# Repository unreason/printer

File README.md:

Printer
=======

Parts and components for a 3D printer

/fsr_endstop - an MSP430-based FSR endstop controller board. More documentation at http://www.unreasonmachines.com/msp430-fsr-endstop-controller-for-3d-printers/

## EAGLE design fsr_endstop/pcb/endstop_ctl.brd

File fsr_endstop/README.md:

FSR_endstop
=======

This is a small controller board for FSR bed leveling sensors for delta 3D printers such as Kossel. More detailed documentation at http://www.unreasonmachines.com/msp430-fsr-endstop-controller-for-3d-printers/.

This specific revision of the PCB hasn't been tested yet (PCBs have been ordered already) - but an earlier version with identical schematics but different layout is running just fine in my Kossel right now. Still, use at your own risk.

## Bill of materials

Name     | Part #                                | Qty |
---------|---------------------------------------|-----|
C1       | 100n 0603 capacitor                   | 1   | 
J1       | 3-pin JST PH right angle connector    | 1   | 
J2,J3,J4 | 2-pin JST PH right angle connector    | 3   |
J5       | 6-pin 1.27mm right angle connector    | 1   |
R1,R2,R3 | 10K 0603 resistor                     | 3   |
R4       | 1.5K 0603 resistor                    | 1   |
R5       | 47K 0603 resistor                     | 1   |
TOUCH    | 0603 2mA LED                          | 1   |
U1       | MSP430G2553 MCU, 20-pin SSOP          | 1   |

Tested with Interlink 30-81794 FSRs, but any similar sized FSR should work, possibly with minor changes to the filter coefficients in code.

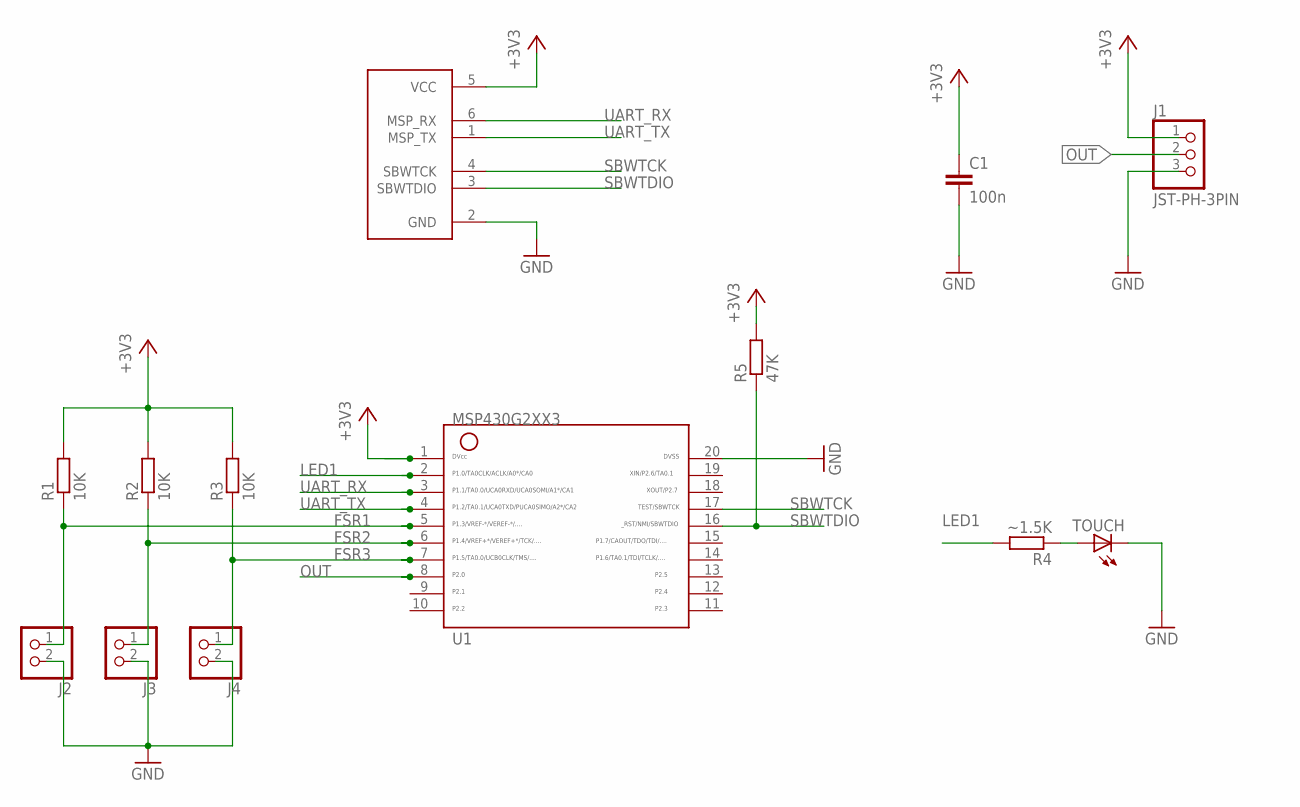
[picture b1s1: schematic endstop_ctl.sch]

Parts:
C1: 100n; C0603
J1: JST-PH-3PIN; JST-PH-3PIN-PTH-RA
J2, J3, J4: JST_2PIN-THM-RA; JST-PH-2-THM-RA
J5: MSP-SBWPTH; MSP-SBW-0.05-PTH-90DEG
R1, R2, R3: 10K; R0603
R4: ~1.5K; R0603
R5: 47K; R0603
TOUCH: LED0603; LED-0603
U1: G2XX3---PW20; PW20

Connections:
+3V3: C1.1, J1.1, J5.5 (VCC), R1.2, R2.2, R3.2, R5.2, U1.1
FSR1: J2.1 (2), R1.1, U1.5
FSR2: J3.1 (2), R2.1, U1.6
FSR3: J4.1 (2), R3.1, U1.7
GND: C1.2, J1.3, J2.2 (1), J3.2 (1), J4.2 (1), J5.2 (GND), TOUCH.C, U1.20
LED1: R4.2, U1.2
unnamed: R4.1, TOUCH.A
OUT: J1.2, U1.8
SBWTCK: J5.4 (SBWTCK), U1.17
SBWTDIO: J5.3 (SBWTDIO), R5.1, U1.16
UART_RX: J5.6 (MSP_RX), U1.3
UART_TX: J5.1 (MSP_TX), U1.4

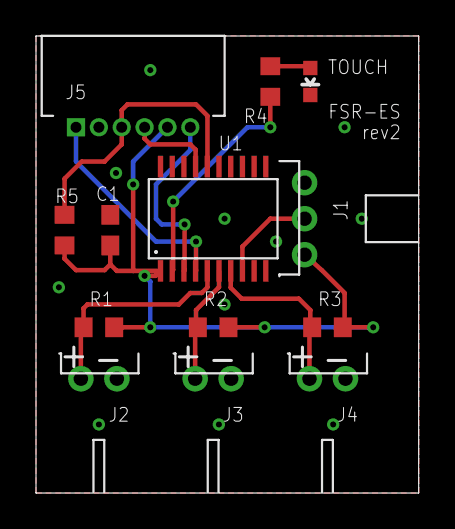
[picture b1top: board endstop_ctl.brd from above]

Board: 2 copper layers, 21.3 x 25.4 mm, 13 parts (0 on the bottom side), 12 nets.

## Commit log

2014-09-24 FSR endstop board
2014-09-24 Added doc link

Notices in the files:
parts and their libraries:
SparkFun-LED: Licensing: CC v3.0 Share-Alike You are welcome to use this library for commercial purposes.
